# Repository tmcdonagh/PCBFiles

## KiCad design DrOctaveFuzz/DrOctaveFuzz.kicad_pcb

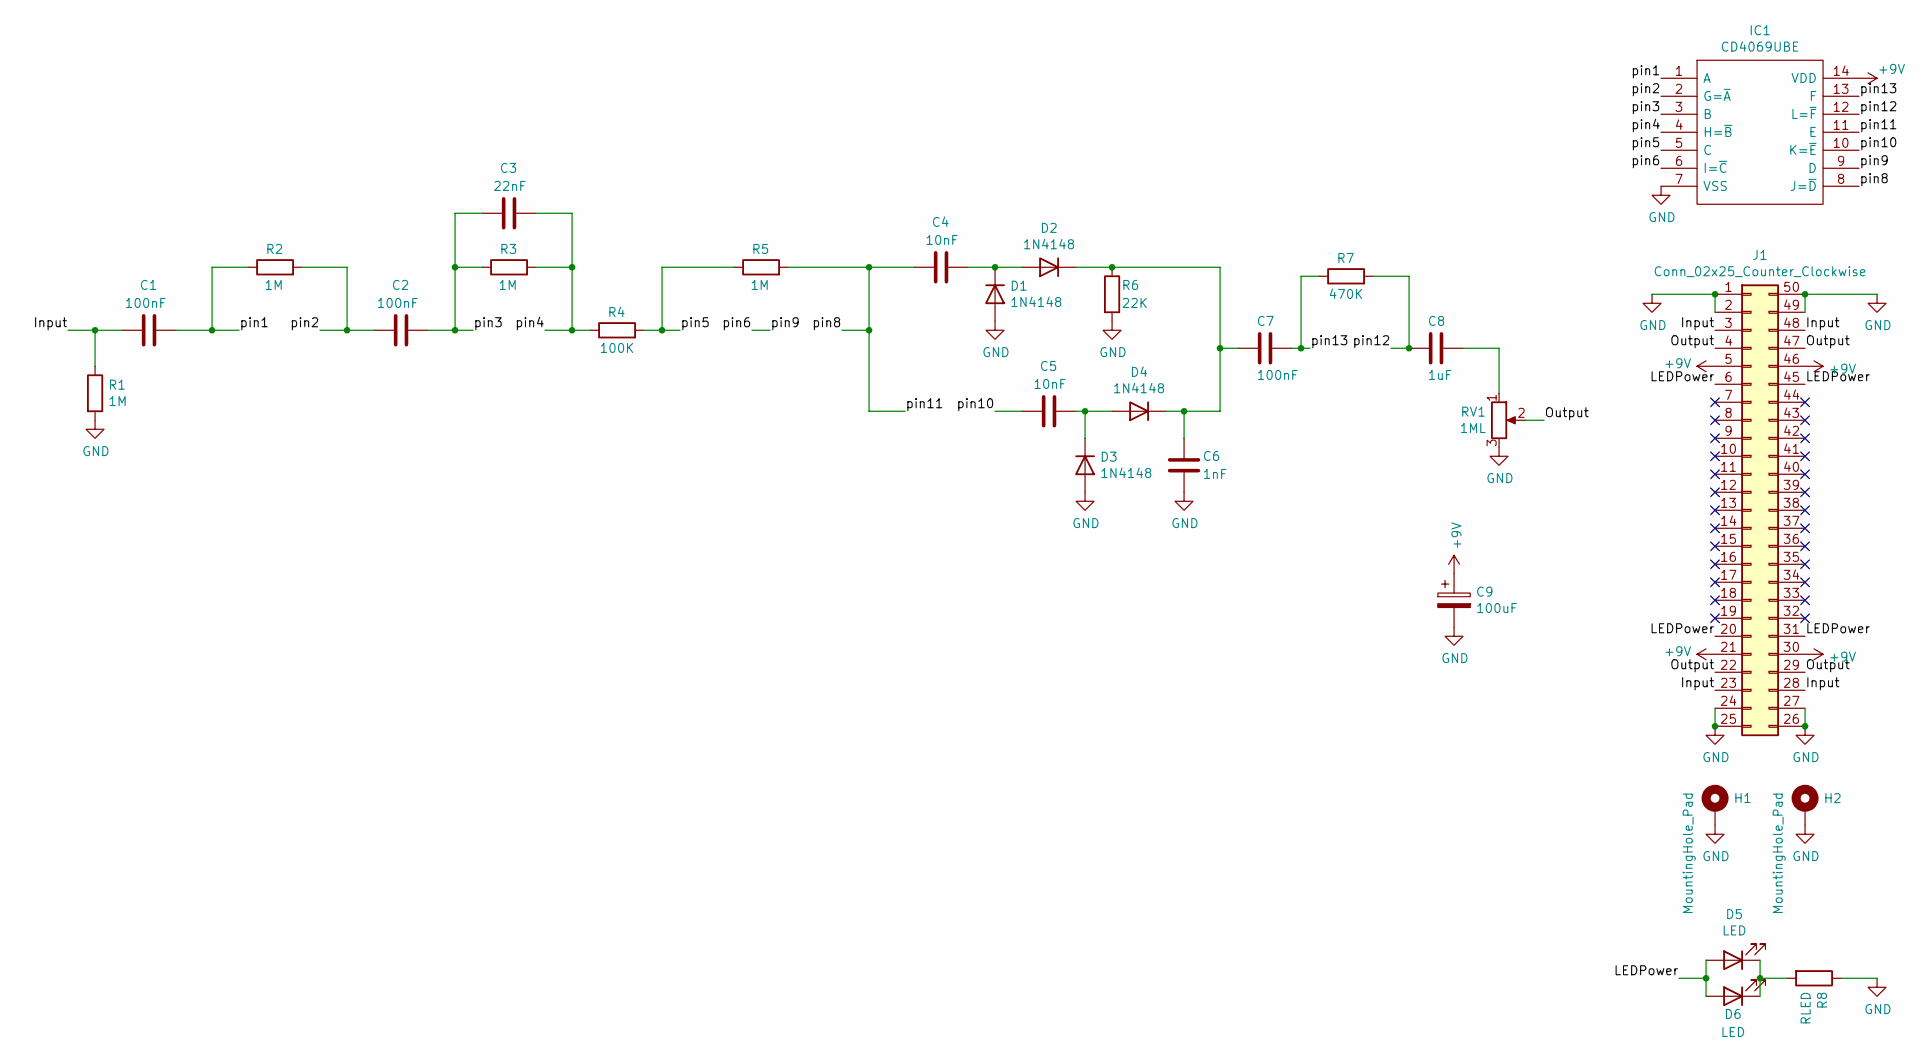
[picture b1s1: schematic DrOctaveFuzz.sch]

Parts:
C1, C2, C7: 100nF; C_Flat_L7.2_H6.5
C3: 22nF; C_Flat_L7.2_H6.5
C4, C5: 10nF; C_Flat_L7.2_H6.5
C6: 1nF; C_Flat_L7.2_H6.5
C8: 1uF; C_Flat_L7.2_H10
C9: 100uF; CP_Radial_D6.3mm_P2.00mm_L11.0mm
D1, D2, D3, D4: 1N4148; D_DO-35_SOD27_P7.62mm_Horizontal
D5, D6: LED; LED_D5.0mm
H1, H2: MountingHole_Pad; MountingHole_2.5mm_Pad
IC1: CD4069UBE; DIP-14_W7.62mm; Mouser Part Number 595-CD4069UBE
J1: Conn_02x25_Counter_Clockwise; N64-Connector-Wide
R1, R2, R3, R5: 1M; R_Axial_DIN0207_L6.3mm_D2.5mm_P10.16mm_Horizontal
R4: 100K; R_Axial_DIN0207_L6.3mm_D2.5mm_P10.16mm_Horizontal
R6: 22K; R_Axial_DIN0207_L6.3mm_D2.5mm_P10.16mm_Horizontal
R7: 470K; R_Axial_DIN0207_L6.3mm_D2.5mm_P10.16mm_Horizontal
R8: RLED; R_Axial_DIN0207_L6.3mm_D2.5mm_P10.16mm_Horizontal
RV1: 1ML; Potentiometer_Bourns_PTV09A-1_Single_Vertical

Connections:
+9V: C9.1, IC1.14 (VDD), J1.5, J1.21, J1.30, J1.46
/Input: C1.1, J1.3, J1.23, J1.28, J1.48, R1.1
/LEDPower: D5.2 (A), D6.2 (A), J1.6, J1.20, J1.31, J1.45
/Output: J1.4, J1.22, J1.29, J1.47, RV1.2
/pin1: C1.2, IC1.1 (A), R2.1
/pin2: C2.1, IC1.2 (G=~A), R2.2
/pin3: C2.2, C3.1, IC1.3 (B), R3.1
/pin4: C3.2, IC1.4 (H=~B), R3.2, R4.1
/pin5: IC1.5 (C), R4.2, R5.1
/pin6: IC1.6 (I=~C), IC1.9 (D)
/pin10: C5.1, IC1.10 (K=~E)
/pin11: C4.1, IC1.8 (J=~D), IC1.11 (E), R5.2
/pin12: C8.2, IC1.12 (L=~F), R7.2
/pin13: C7.1, IC1.13 (F), R7.1
GND: C6.2, C9.2, D1.2 (A), D3.2 (A), H1.1, H2.1, IC1.7 (VSS), J1.1, J1.2, J1.24, J1.25, J1.26, J1.27, J1.49, J1.50, R1.2, R6.2, R8.1, RV1.3
unnamed: C4.2, D1.1 (K), D2.2 (A)
unnamed: C5.2, D3.1 (K), D4.2 (A)
unnamed: C6.1, C7.2, D2.1 (K), D4.1 (K), R6.1
unnamed: C8.1, RV1.1
unnamed: D5.1 (K), D6.1 (K), R8.2

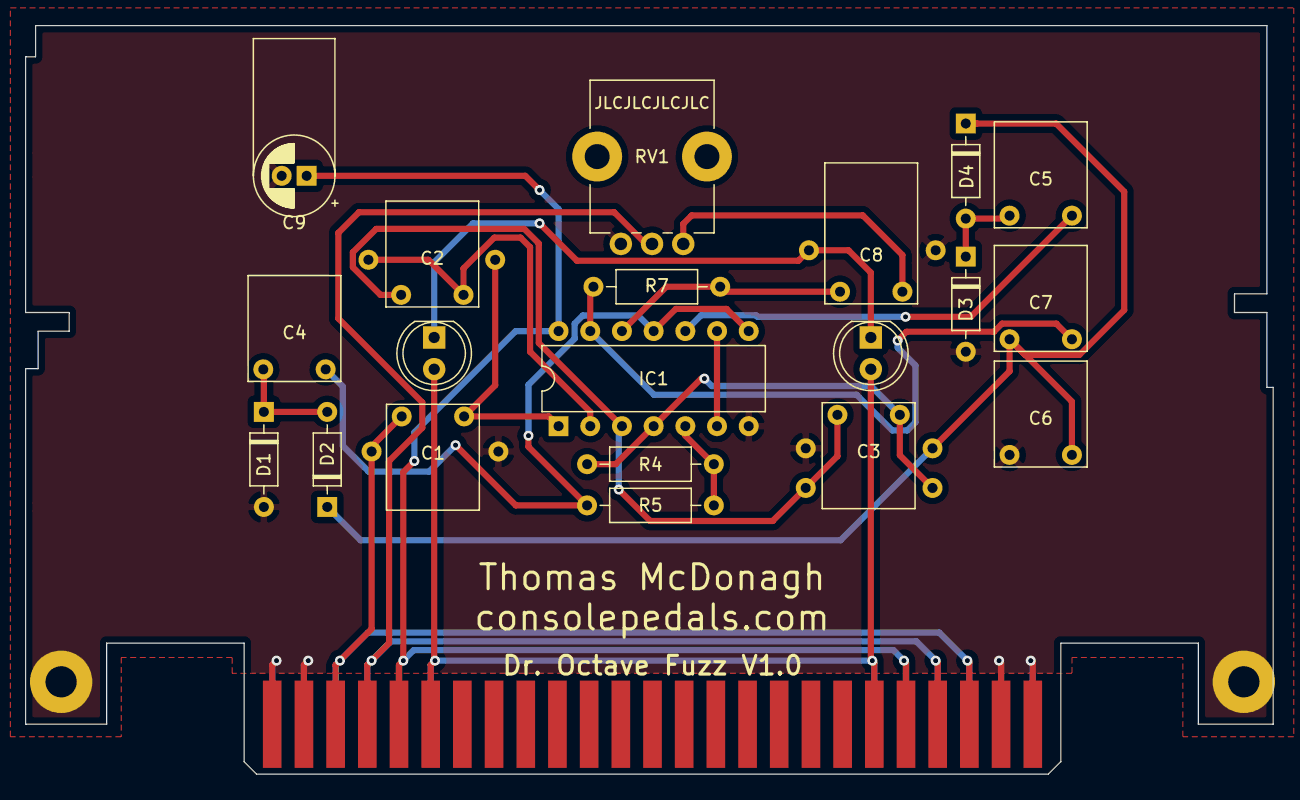
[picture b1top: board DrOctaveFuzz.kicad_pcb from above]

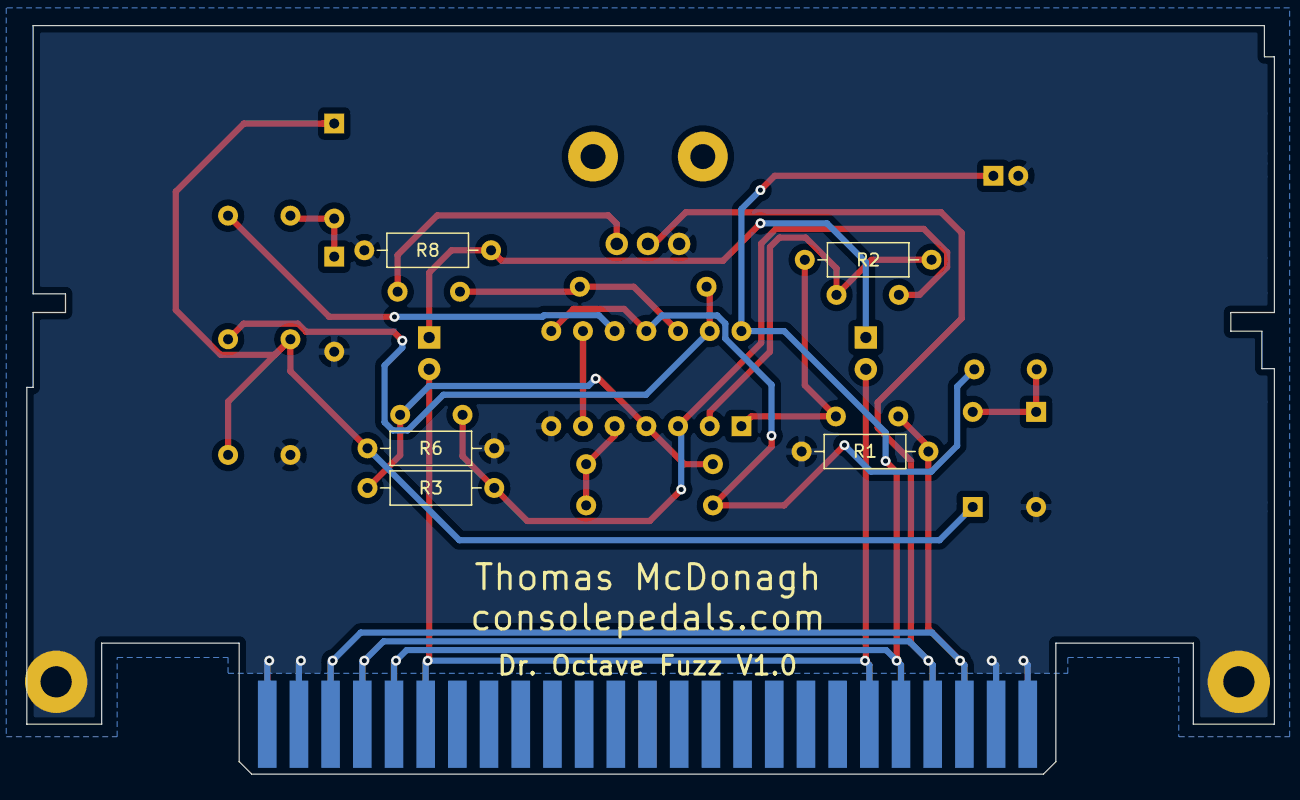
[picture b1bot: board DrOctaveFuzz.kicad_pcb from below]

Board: 2 copper layers, 100.0 x 60.0 mm, 28 parts (5 on the bottom side), 20 nets.

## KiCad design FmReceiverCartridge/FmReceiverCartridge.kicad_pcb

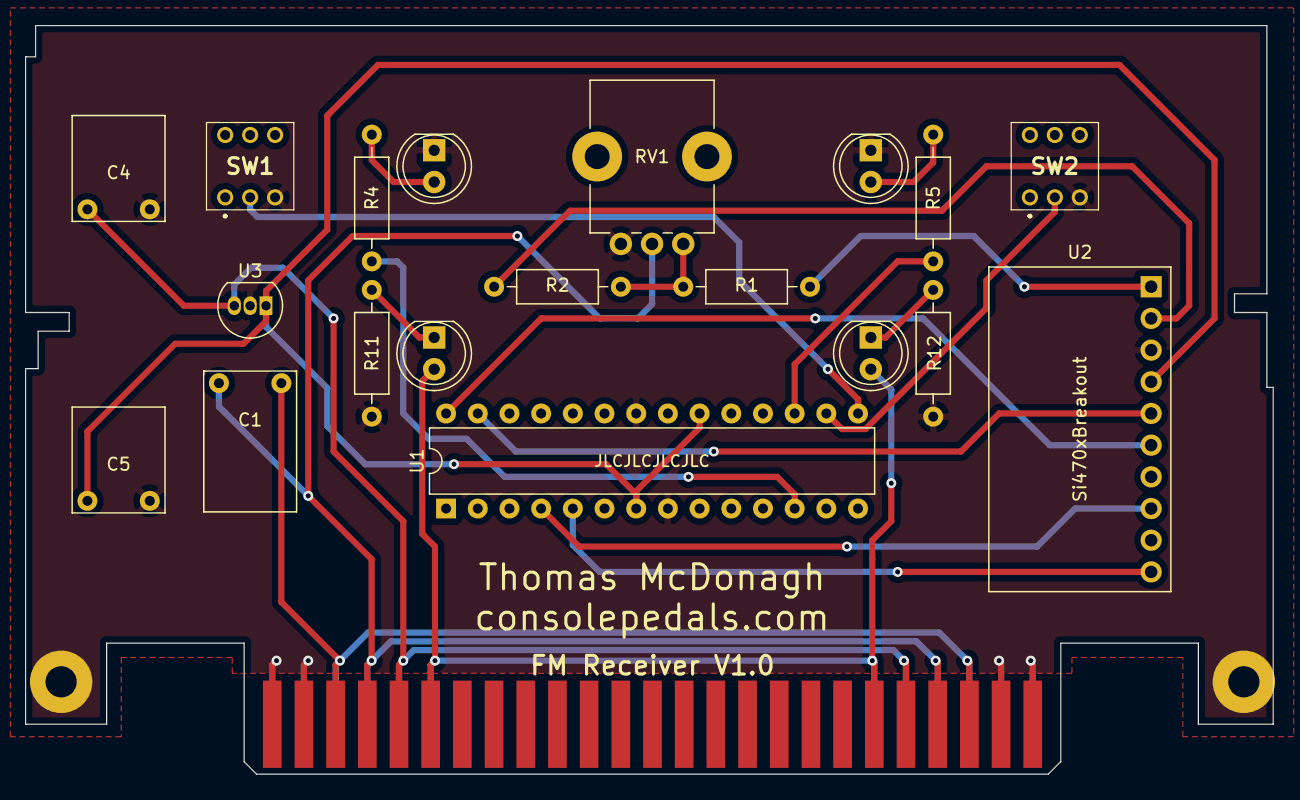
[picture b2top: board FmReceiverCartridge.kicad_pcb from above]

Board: 2 copper layers, 100.0 x 60.0 mm, 22 parts (0 on the bottom side), 21 nets.

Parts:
C1: 1uF; C_Flat_L7.2_H10
C4: 0.33uF; C_Flat_L7.2_H6.5
C5: 0.1uF; C_Flat_L7.2_H6.5
D1, D2, D4, D5: LED; LED_D5.0mm
H1, H2: MountingHole_Pad; MountingHole_2.5mm_Pad
J2: Conn_02x25_Counter_Clockwise; N64-Connector-Wide
R1, R2: 100R; R_Axial_DIN0207_L6.3mm_D2.5mm_P10.16mm_Horizontal
R4, R5, R11, R12: RLED; R_Axial_DIN0207_L6.3mm_D2.5mm_P10.16mm_Horizontal
RV1: 500K; Potentiometer_Bourns_PTV09A-1_Single_Vertical
SW1: SW_A; TL2230OAF140
SW2: SW_B; TL2230OAF140
U1: ATmega328P-PU; DIP-28_W7.62mm
U2: Si470xBreakout
U3: L78L33_TO92; TO-92_Inline

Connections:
+3V3: C5.2, U1.7, U1.20, U2.4, U3.1
+9V: C4.2, J2.5, J2.21, J2.30, J2.46, U3.3
/D2: U1.4, U2.8
/D3: U1.5, U2.10
/Input: C1.2, J2.3, J2.23, J2.28, J2.48
/LEDPower: D4.2, D5.2, J2.6, J2.20, J2.31, J2.45
/LED_A: R4.1, U1.12
/LED_B: R5.1, U1.17
/Output: C1.1, J2.4, J2.22, J2.29, J2.47, RV1.2
/SCL: U1.28, U2.6
/SDA: U1.27, U2.5
/SW_A: SW1.2, U1.15
/SW_B: SW2.2, U1.16
GND: C4.1, C5.1, D1.1, D2.1, H1.1, H2.1, J2.1, J2.2, J2.24, J2.25, J2.26, J2.27, J2.49, J2.50, R11.1, R12.2, RV1.3, SW1.3, SW2.3, U1.8, U1.22, U2.3, U3.2
unnamed: D1.2, R4.2
unnamed: D2.2, R5.2
unnamed: D4.1, R11.2
unnamed: D5.1, R12.1
unnamed: R1.1, R2.2, RV1.1
unnamed: R1.2, U2.1
unnamed: R2.1, U2.2

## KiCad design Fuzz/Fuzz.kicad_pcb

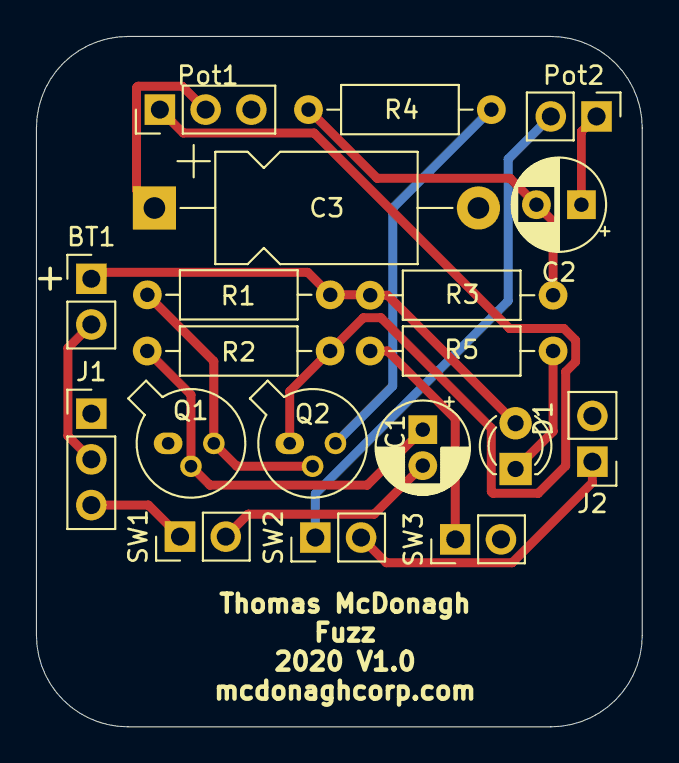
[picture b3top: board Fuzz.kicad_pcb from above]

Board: 2 copper layers, 33.7 x 38.4 mm, 19 parts (0 on the bottom side), 16 nets.

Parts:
BT1: Battery; PinHeader_1x02_P2.54mm_Vertical
C1: 2.2uf; CP_Radial_D5.0mm_P2.00mm
C2: 0.01uf; CP_Radial_D5.0mm_P2.50mm
C3: 22uf; CP_Axial_L11.0mm_D6.0mm_P18.00mm_Horizontal
D1: LED; LED_D3.0mm
J1: AudioJack3; PinHeader_1x03_P2.54mm_Vertical
J2: AudioJack2; PinHeader_1x02_P2.54mm_Vertical
Pot1: 1K; PinHeader_1x03_P2.54mm_Vertical
Pot2: 500K; PinHeader_1x02_P2.54mm_Vertical
Q1, Q2: BC109; TO-18-3
R1: 33K; R_Axial_DIN0207_L6.3mm_D2.5mm_P10.16mm_Horizontal
R2, R5: 100K; R_Axial_DIN0207_L6.3mm_D2.5mm_P10.16mm_Horizontal
R3: 330; R_Axial_DIN0207_L6.3mm_D2.5mm_P10.16mm_Horizontal
R4: 8.2K; R_Axial_DIN0207_L6.3mm_D2.5mm_P10.16mm_Horizontal
SW1, SW2, SW3: SW_SPST; PinHeader_1x02_P2.54mm_Vertical

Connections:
GND: C3.2, J1.1, J2.2, Pot1.3, Q1.1, SW3.2
unnamed: BT1.1, D1.2, R1.2, R3.2
unnamed: BT1.2, J1.2
unnamed: C1.1, Q1.2, R2.1
unnamed: C1.2, SW1.2
unnamed: C2.1, Pot2.1
unnamed: C2.2, R3.1, R4.1
unnamed: C3.1, Pot1.2
unnamed: D1.1, R5.2
unnamed: J1.3, SW1.1
unnamed: J2.1, SW2.2
unnamed: Pot1.1, Q2.1, R2.2
unnamed: Pot2.2, SW2.1
unnamed: Q1.3, Q2.2, R1.1
unnamed: Q2.3, R4.2
unnamed: R5.1, SW3.1

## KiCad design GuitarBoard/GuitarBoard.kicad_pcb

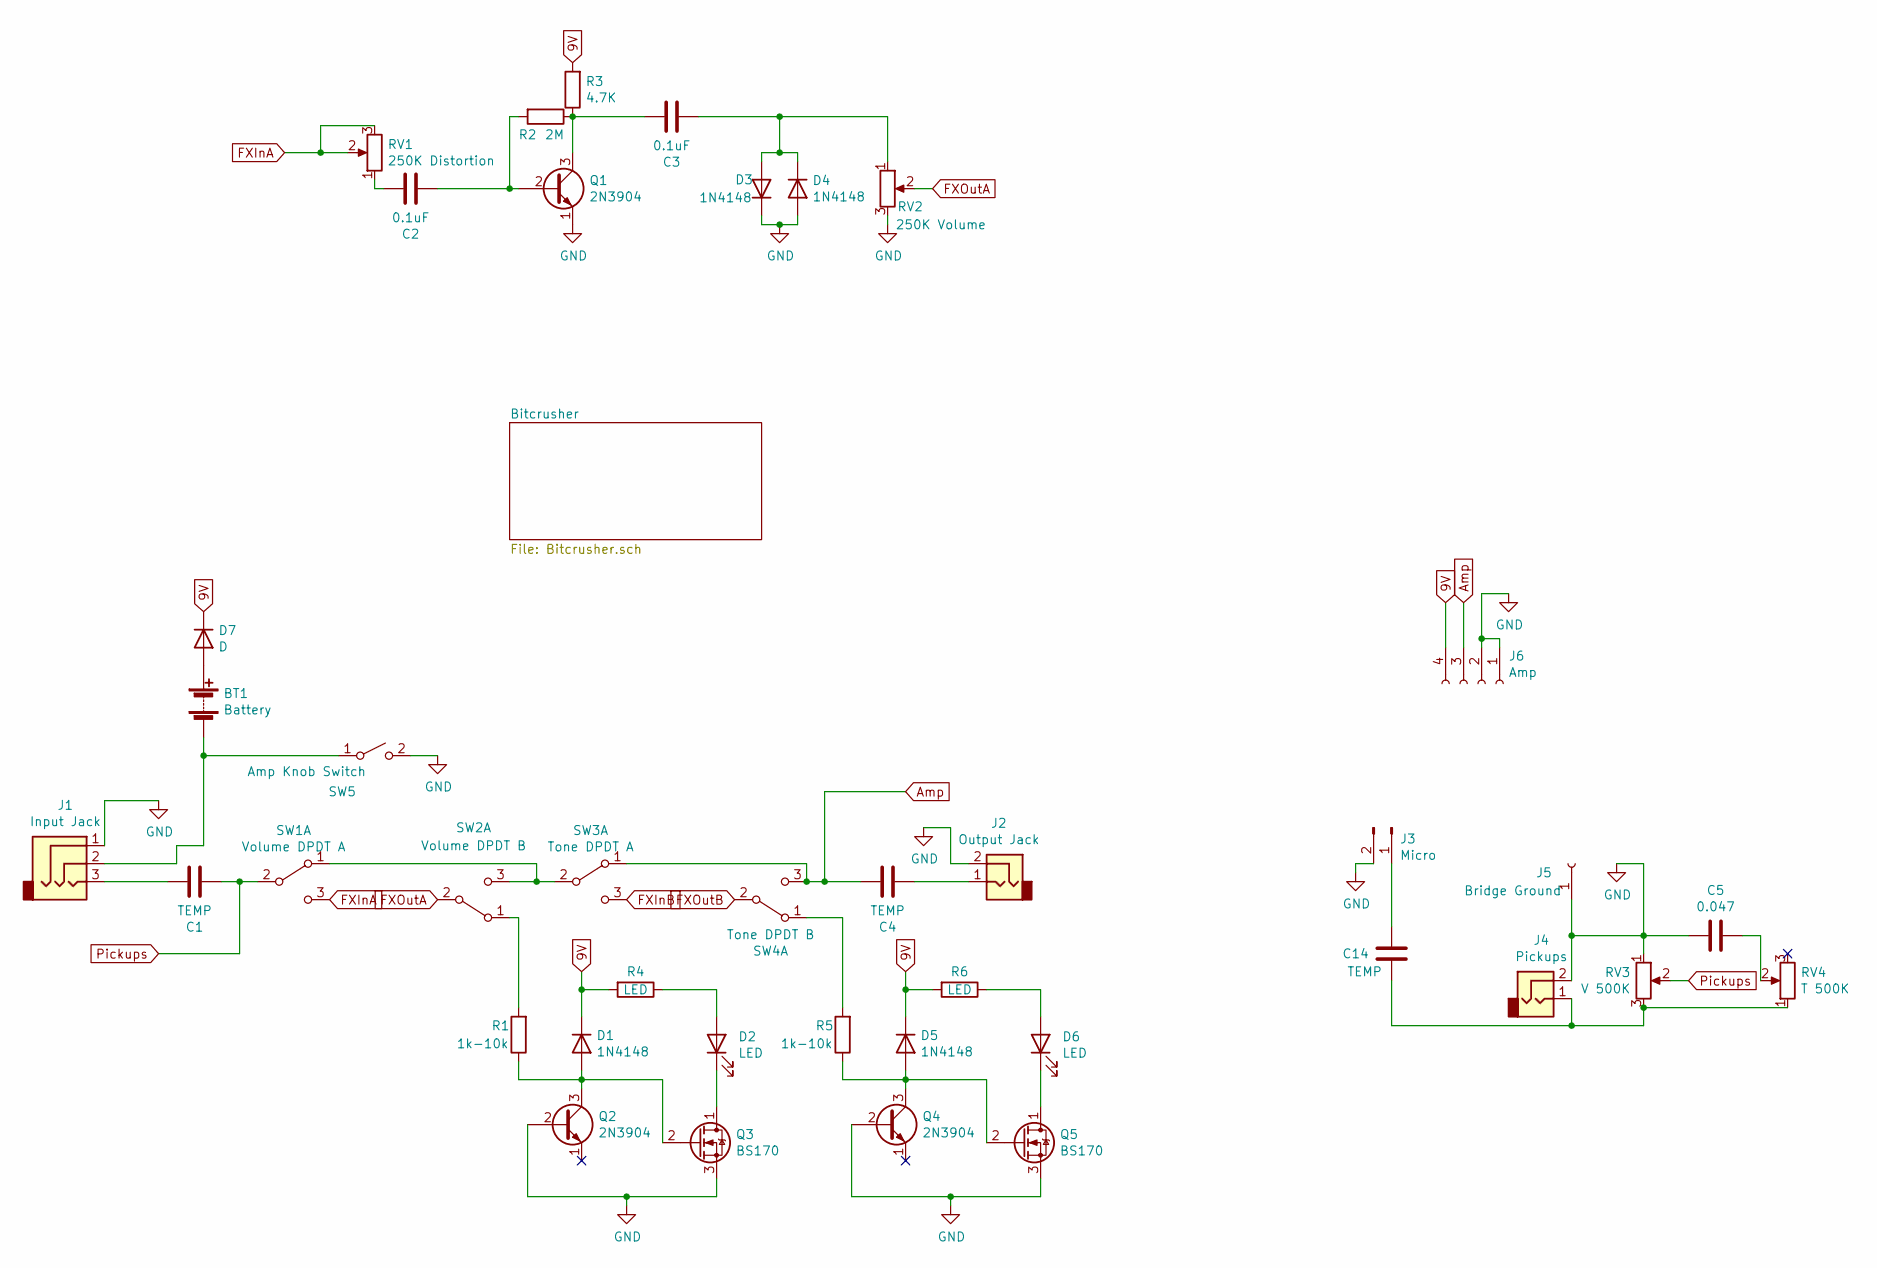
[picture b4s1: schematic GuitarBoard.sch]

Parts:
BT1: Battery; TerminalBlock_bornier-2_P5.08mm
C1, C4: TEMP; C_Flat_L7.2_H10
C2, C3: 0.1uF; C_Rect_L7.2mm_W2.5mm_P5.00mm_FKS2_FKP2_MKS2_MKP2
C5: 0.047; C_Rect_L7.2mm_W2.5mm_P5.00mm_FKS2_FKP2_MKS2_MKP2
C14: TEMP; C_Rect_L7.2mm_W2.5mm_P5.00mm_FKS2_FKP2_MKS2_MKP2
D1, D3, D4, D5: 1N4148; D_DO-35_SOD27_P7.62mm_Horizontal
D2, D6: LED; PinSocket_1x02_P2.54mm_Vertical
D7: D; D_DO-41_SOD81_P10.16mm_Horizontal
J1: Input Jack; PinSocket_1x03_P2.54mm_Vertical
J2: Output Jack; PinSocket_1x02_P2.54mm_Vertical
J3: Micro; TerminalBlock_bornier-2_P5.08mm
J4: Pickups; TerminalBlock_bornier-2_P5.08mm
J5: Bridge Ground; TerminalBlock_bornier-2_P5.08mm
J6: Amp; TerminalBlock_bornier-4_P5.08mm
Q1, Q2, Q4: 2N3904; TO-92_Inline
Q3, Q5: BS170; TO-92_Inline
R1, R5: 1k-10k; R_Axial_DIN0207_L6.3mm_D2.5mm_P10.16mm_Horizontal
R2: 2M; R_Axial_DIN0207_L6.3mm_D2.5mm_P10.16mm_Horizontal
R3: 4.7K; R_Axial_DIN0207_L6.3mm_D2.5mm_P10.16mm_Horizontal
R4, R6: LED; R_Axial_DIN0207_L6.3mm_D2.5mm_P10.16mm_Horizontal
RV1: 250K Distortion; Potentiometer_Bourns_3386F_Vertical
RV2: 250K Volume; Potentiometer_Bourns_3386F_Vertical
RV3: V 500K; PinSocket_1x03_P2.54mm_Vertical
RV4: T 500K; PinSocket_1x03_P2.54mm_Vertical
SW1: Volume DPDT A; PinSocket_1x03_P2.54mm_Vertical
SW2: Volume DPDT B; PinSocket_1x03_P2.54mm_Vertical
SW3: Tone DPDT A; PinSocket_1x03_P2.54mm_Vertical
SW4: Tone DPDT B; PinSocket_1x03_P2.54mm_Vertical
SW5: Amp Knob Switch; PinSocket_1x02_P2.54mm_Vertical

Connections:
9V: D1.1 (K), D5.1 (K), D7.1 (K), J6.4, R3.2, R4.2, R6.2; also elsewhere on the board
Amp: C4.1, J6.3, SW3.1 (A), SW4.3 (C)
FXInA: RV1.2, RV1.3, SW1.3 (C)
FXInB: SW3.3 (C); also elsewhere on the board
FXOutA: RV2.2, SW2.2 (B)
FXOutB: SW4.2 (B); also elsewhere on the board
GND: C5.2, D3.1 (K), D4.2 (A), J1.1, J2.2, J3.2, J4.2, J5.1, J6.1, J6.2, Q1.1 (E), Q2.2 (B), Q3.3 (S), Q4.2 (B), Q5.3 (S), RV2.3, RV3.1, SW5.2 (B); also elsewhere on the board
unnamed: BT1.1 (+), D7.2 (A)
unnamed: BT1.2 (-), J1.2, SW5.1 (A)
unnamed: C1.1, J1.3
unnamed: C2.1, RV1.1
unnamed: C2.2, Q1.2 (B), R2.2
unnamed: C3.1, Q1.3 (C), R2.1, R3.1
unnamed: C3.2, D3.2 (A), D4.1 (K), RV2.1
unnamed: C4.2, J2.1
unnamed: C5.1, RV4.2
unnamed: C14.1, J3.1
unnamed: C14.2, J4.1, RV3.3, RV4.1
unnamed: D1.2 (A), Q2.3 (C), Q3.2 (G), R1.1
unnamed: D2.1 (K), Q3.1 (D)
unnamed: D2.2 (A), R4.1
unnamed: D5.2 (A), Q4.3 (C), Q5.2 (G), R5.1
unnamed: D6.1 (K), Q5.1 (D)
unnamed: D6.2 (A), R6.1
unnamed: R1.2, SW2.1 (A)
unnamed: R5.2, SW4.1 (A)
unnamed: SW1.1 (A), SW2.3 (C), SW3.2 (B)
Pickups: C1.2, RV3.2, SW1.2 (B)

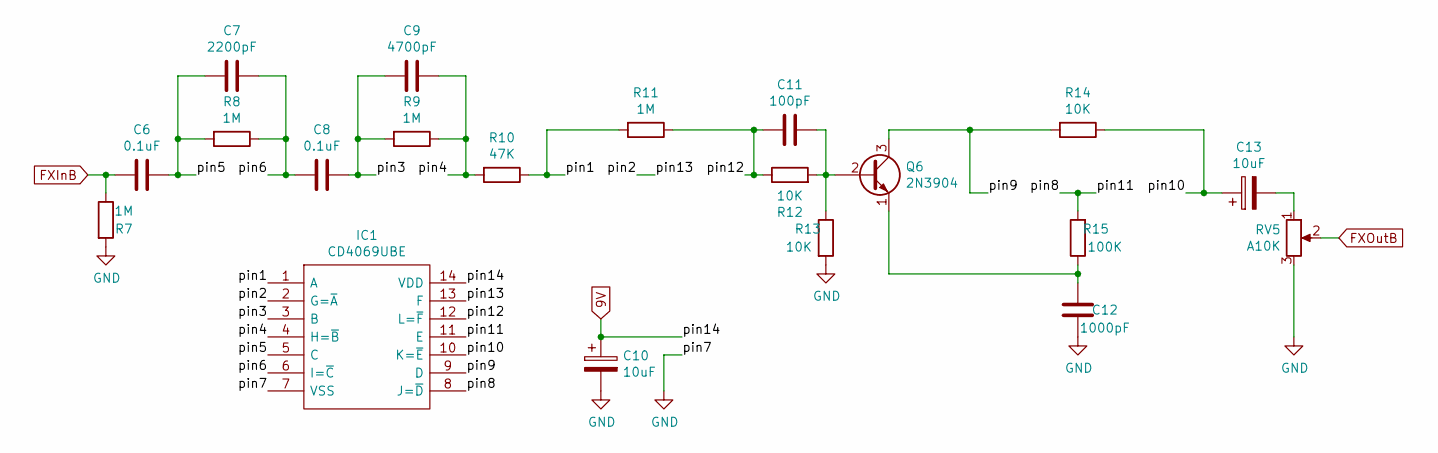
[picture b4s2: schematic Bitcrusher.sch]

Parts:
C6, C8: 0.1uF; C_Rect_L7.2mm_W2.5mm_P5.00mm_FKS2_FKP2_MKS2_MKP2
C7: 2200pF; C_Rect_L7.2mm_W2.5mm_P5.00mm_FKS2_FKP2_MKS2_MKP2
C9: 4700pF; C_Rect_L7.2mm_W2.5mm_P5.00mm_FKS2_FKP2_MKS2_MKP2
C10, C13: 10uF; CP_Radial_D6.3mm_P2.50mm
C11: 100pF; C_Rect_L7.2mm_W2.5mm_P5.00mm_FKS2_FKP2_MKS2_MKP2
C12: 1000pF; C_Rect_L7.2mm_W2.5mm_P5.00mm_FKS2_FKP2_MKS2_MKP2
IC1: CD4069UBE; DIP794W53P254L1930H508Q14N; Mouser Part Number 595-CD4069UBE
Q6: 2N3904; TO-92_Inline
R7, R8, R9, R11: 1M; R_Axial_DIN0207_L6.3mm_D2.5mm_P10.16mm_Horizontal
R10: 47K; R_Axial_DIN0207_L6.3mm_D2.5mm_P10.16mm_Horizontal
R12, R13, R14: 10K; R_Axial_DIN0207_L6.3mm_D2.5mm_P10.16mm_Horizontal
R15: 100K; R_Axial_DIN0207_L6.3mm_D2.5mm_P10.16mm_Horizontal
RV5: A10K; Potentiometer_Bourns_3386F_Vertical

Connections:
9V: C10.1, IC1.14 (VDD); also elsewhere on the board
/Bitcrusher/pin1: IC1.1 (A), R10.1, R11.2
/Bitcrusher/pin3: C8.1, C9.2, IC1.3 (B), R9.2
/Bitcrusher/pin4: C9.1, IC1.4 (H=~B), R9.1, R10.2
/Bitcrusher/pin5: C6.1, C7.2, IC1.5 (C), R8.2
/Bitcrusher/pin6: C7.1, C8.2, IC1.6 (I=~C), R8.1
/Bitcrusher/pin9: IC1.9 (D), Q6.3 (C), R14.2
/Bitcrusher/pin10: C13.1, IC1.10 (K=~E), R14.1
/Bitcrusher/pin11: IC1.8 (J=~D), IC1.11 (E), R15.2
/Bitcrusher/pin12: C11.2, IC1.12 (L=~F), R11.1, R12.1
/Bitcrusher/pin13: IC1.2 (G=~A), IC1.13 (F)
FXInB: C6.2, R7.1; also elsewhere on the board
FXOutB: RV5.2; also elsewhere on the board
GND: C10.2, C12.1, IC1.7 (VSS), R7.2, R13.2, RV5.3; also elsewhere on the board
unnamed: C11.1, Q6.2 (B), R12.2, R13.1
unnamed: C12.2, Q6.1 (E), R15.1
unnamed: C13.2, RV5.1

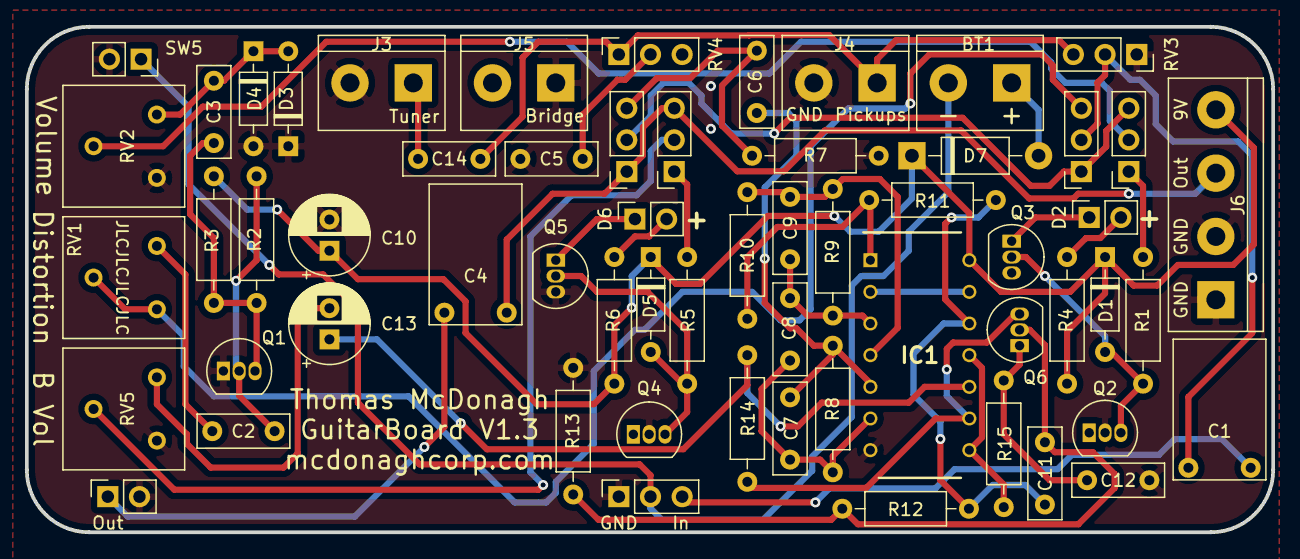
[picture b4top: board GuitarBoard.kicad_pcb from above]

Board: 2 copper layers, 100.0 x 40.6 mm, 60 parts (0 on the bottom side), 41 nets.

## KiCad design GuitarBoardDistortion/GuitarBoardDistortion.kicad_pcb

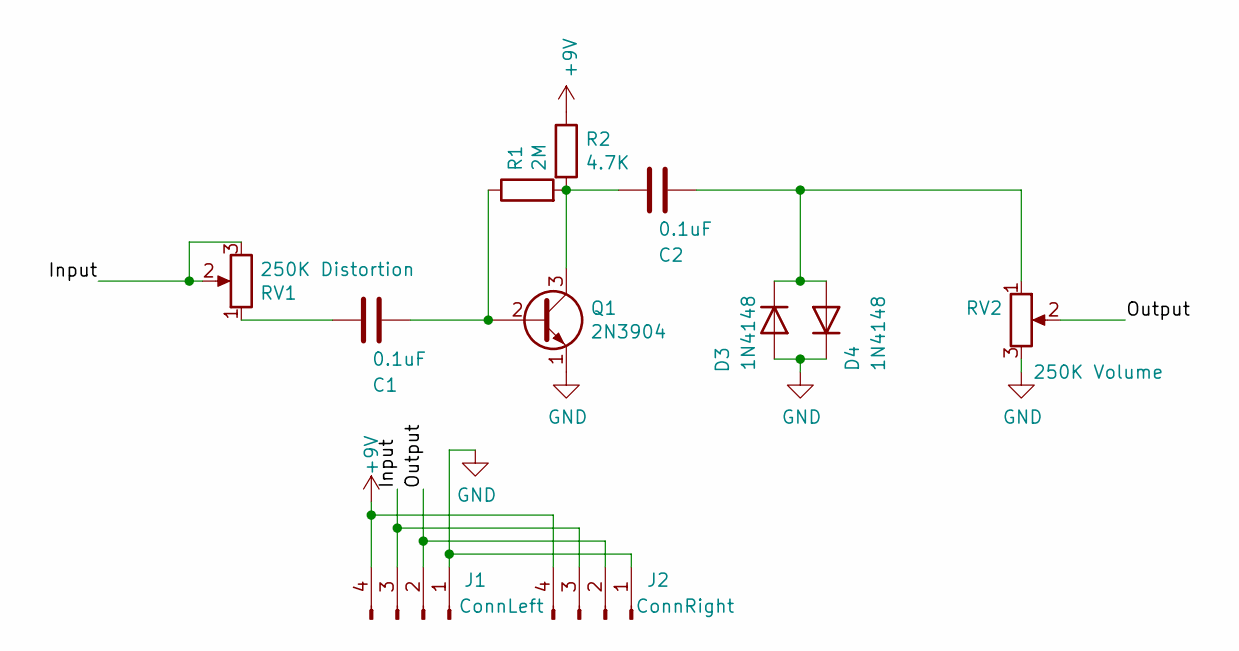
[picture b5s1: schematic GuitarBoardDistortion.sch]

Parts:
C1, C2: 0.1uF; C_Disc_D10.5mm_W5.0mm_P7.50mm
D3, D4: 1N4148; D_DO-35_SOD27_P7.62mm_Horizontal
J1: ConnLeft; PinSocket_1x04_P2.54mm_Vertical
J2: ConnRight; PinSocket_1x04_P2.54mm_Vertical
Q1: 2N3904; TO-92_Inline
R1: 2M; R_Axial_DIN0207_L6.3mm_D2.5mm_P10.16mm_Horizontal
R2: 4.7K; R_Axial_DIN0207_L6.3mm_D2.5mm_P10.16mm_Horizontal
RV1: 250K Distortion; Potentiometer_Bourns_3386F_Vertical
RV2: 250K Volume; Potentiometer_Bourns_3386F_Vertical

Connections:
+9V: J1.4, J2.4, R2.1
/Input: J1.3, J2.3, RV1.2, RV1.3
/Output: J1.2, J2.2, RV2.2
GND: D3.2 (A), D4.1 (K), J1.1, J2.1, Q1.1 (E), RV2.3
unnamed: C1.1, Q1.2 (B), R1.1
unnamed: C1.2, RV1.1
unnamed: C2.1, D3.1 (K), D4.2 (A), RV2.1
unnamed: C2.2, Q1.3 (C), R1.2, R2.2

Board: 2 copper layers, 11 parts (0 on the bottom side), 8 nets, no tracks yet.

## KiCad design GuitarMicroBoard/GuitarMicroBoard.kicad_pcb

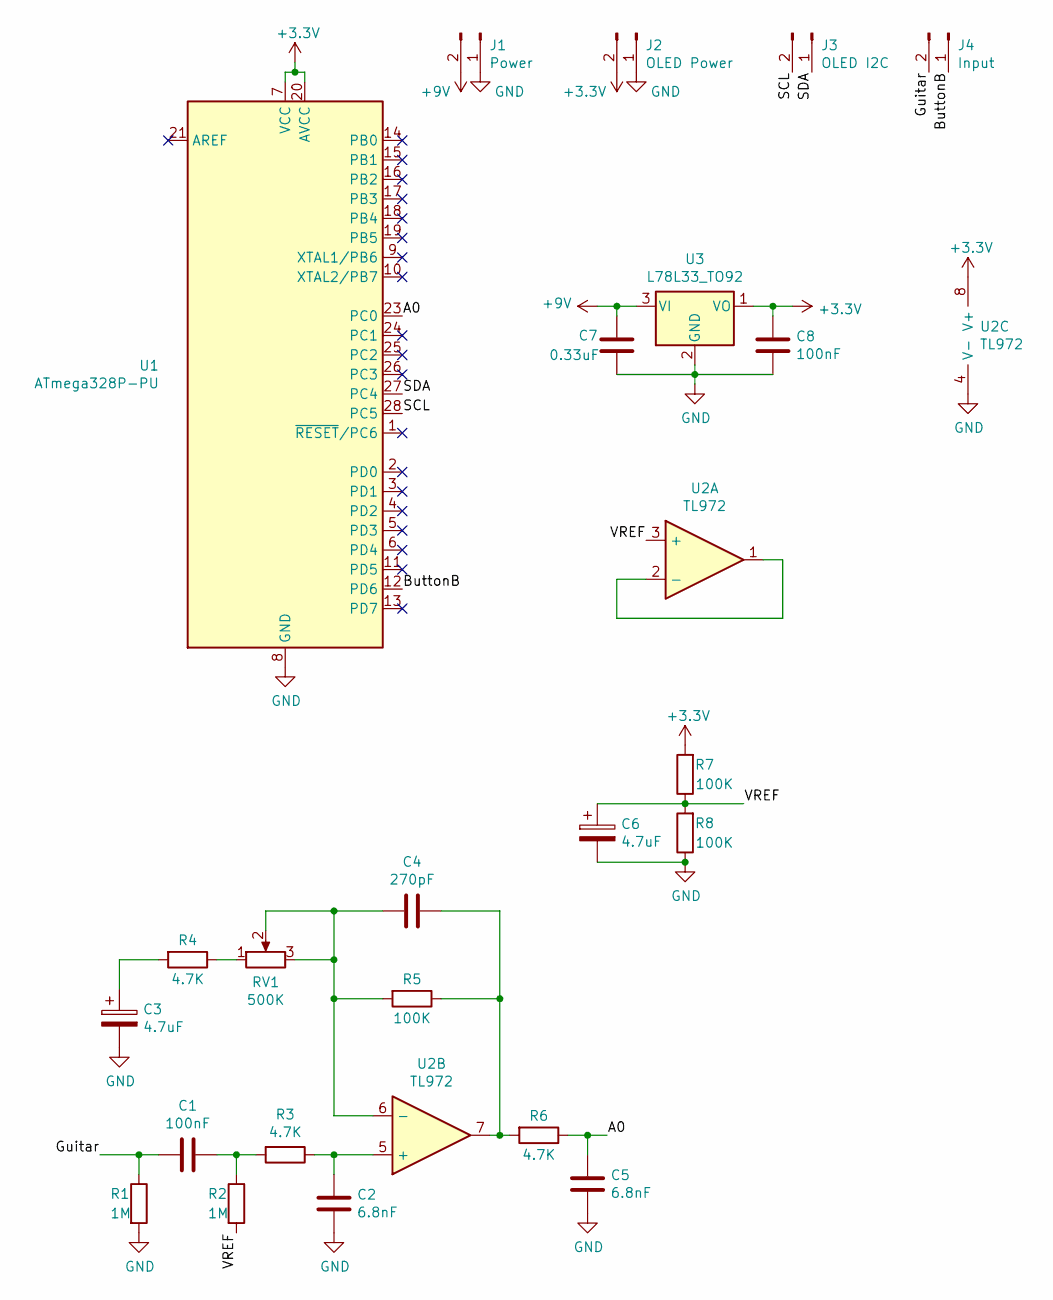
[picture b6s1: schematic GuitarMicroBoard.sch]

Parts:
C1, C8: 100nF; C_Rect_L7.2mm_W2.5mm_P5.00mm_FKS2_FKP2_MKS2_MKP2
C2, C5: 6.8nF; C_Rect_L7.2mm_W2.5mm_P5.00mm_FKS2_FKP2_MKS2_MKP2
C3, C6: 4.7uF; CP_Radial_D5.0mm_P2.00mm_L11.0mm
C4: 270pF; C_Rect_L7.2mm_W2.5mm_P5.00mm_FKS2_FKP2_MKS2_MKP2
C7: 0.33uF; C_Rect_L7.2mm_W2.5mm_P5.00mm_FKS2_FKP2_MKS2_MKP2
J1: Power; PinSocket_1x02_P2.54mm_Vertical
J2: OLED Power; TerminalBlock_bornier-2_P5.08mm
J3: OLED I2C; TerminalBlock_bornier-2_P5.08mm
J4: Input; TerminalBlock_bornier-2_P5.08mm
R1, R2: 1M; R_Axial_DIN0207_L6.3mm_D2.5mm_P10.16mm_Horizontal
R3, R4, R6: 4.7K; R_Axial_DIN0207_L6.3mm_D2.5mm_P10.16mm_Horizontal
R5, R7, R8: 100K; R_Axial_DIN0207_L6.3mm_D2.5mm_P10.16mm_Horizontal
RV1: 500K; Potentiometer_Bourns_3386F_Vertical
U1: ATmega328P-PU; DIP-28_W7.62mm
U2: TL972; DIP-8_W7.62mm
U3: L78L33_TO92; TO-92_Inline

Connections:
+3V3: C8.1, J2.2, R7.2, U1.7 (VCC), U1.20 (AVCC), U2.8 (V+), U3.1 (VO)
+9V: C7.1, J1.2, U3.3 (VI)
/A0: C5.1, R6.1, U1.23 (PC0)
/ButtonB: J4.1, U1.12 (PD6)
/Guitar: C1.2, J4.2, R1.1
/SCL: J3.2, U1.28 (PC5)
/SDA: J3.1, U1.27 (PC4)
/VREF: C6.1, R2.2, R7.1, R8.2, U2.3 (+)
GND: C2.1, C3.2, C5.2, C6.2, C7.2, C8.2, J1.1, J2.1, R1.2, R8.1, U1.8 (GND), U1.22 (GND), U2.4 (V-), U3.2 (GND)
unnamed: C1.1, R2.1, R3.2
unnamed: C2.2, R3.1, U2.5 (+)
unnamed: C3.1, R4.2
unnamed: C4.1, R5.2, RV1.2, RV1.3, U2.6 (-)
unnamed: C4.2, R5.1, R6.2, U2.7
unnamed: R4.1, RV1.1
unnamed: U2.1, U2.2 (-)

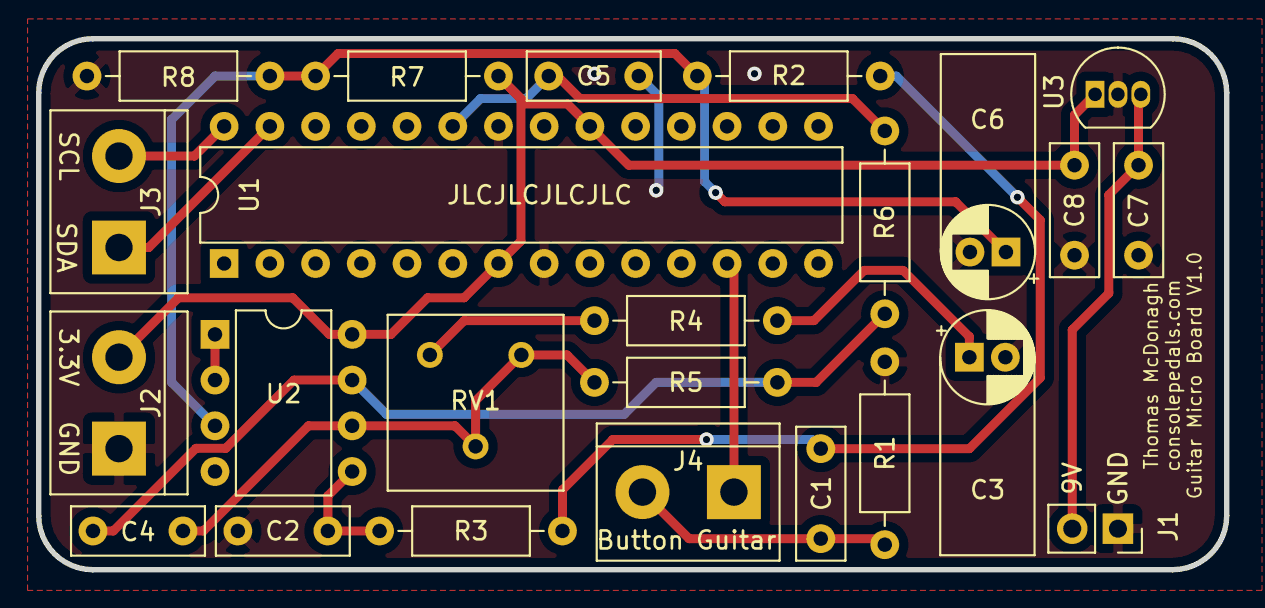
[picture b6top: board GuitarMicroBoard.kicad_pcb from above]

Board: 2 copper layers, 66.0 x 29.5 mm, 24 parts (0 on the bottom side), 16 nets.

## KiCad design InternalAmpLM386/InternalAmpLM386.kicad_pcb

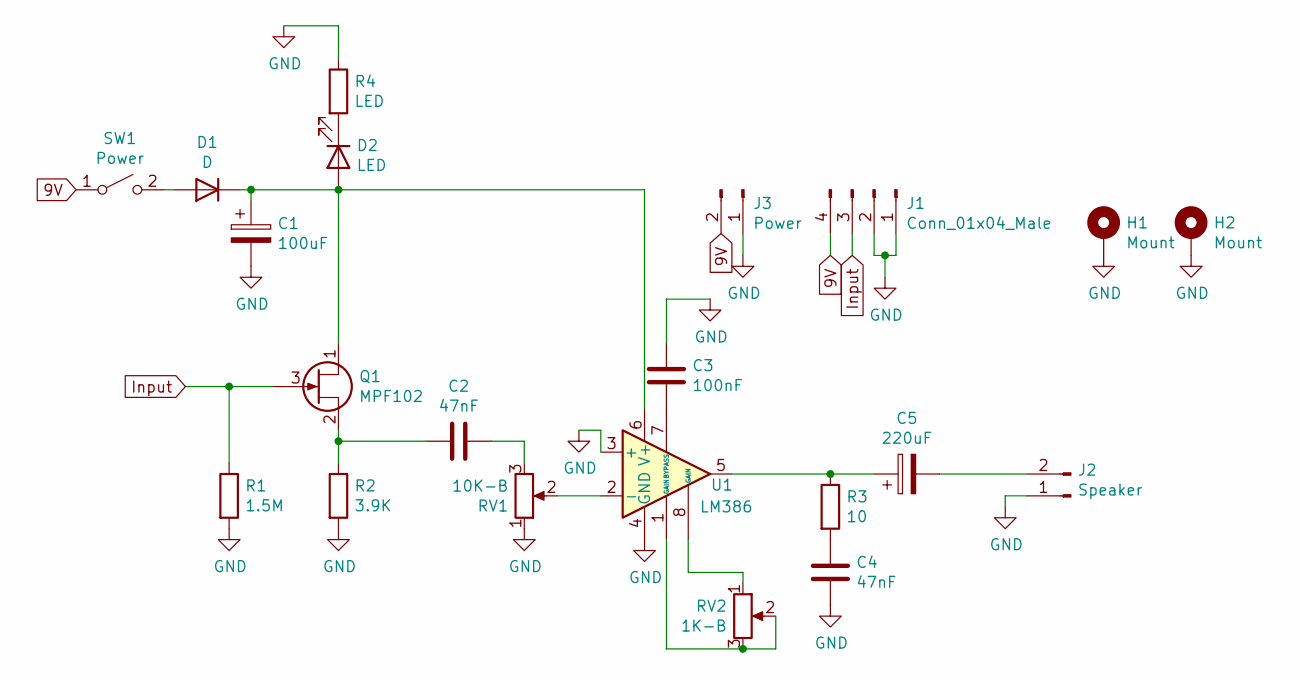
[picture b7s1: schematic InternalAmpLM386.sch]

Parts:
C1: 100uF; CP_Radial_D8.0mm_P3.50mm
C2, C4: 47nF; C_Flat_L7.2_H6.5
C3: 100nF; C_Flat_L7.2_H6.5
C5: 220uF; CP_Radial_D10.0mm_P5.00mm
D1: D; D_DO-41_SOD81_P10.16mm_Horizontal
D2: LED; LED_D5.0mm
H1, H2: Mount; MountingHole_2.7mm_Pad
J1: Conn_01x04_Male; PinSocket_1x04_P2.54mm_Vertical
J2: Speaker; PinSocket_1x02_P2.54mm_Vertical
J3: Power; PinSocket_1x02_P2.54mm_Vertical
Q1: MPF102; TO-92L_Inline
R1: 1.5M; R_Axial_DIN0207_L6.3mm_D2.5mm_P10.16mm_Horizontal
R2: 3.9K; R_Axial_DIN0207_L6.3mm_D2.5mm_P10.16mm_Horizontal
R3: 10; R_Axial_DIN0207_L6.3mm_D2.5mm_P10.16mm_Horizontal
R4: LED; R_Axial_DIN0207_L6.3mm_D2.5mm_P10.16mm_Horizontal
RV1: 10K-B; PinHeader_1x03_P2.54mm_Vertical
RV2: 1K-B; Potentiometer_Bourns_3386F_Vertical
SW1: Power; PinHeader_1x02_P2.54mm_Vertical
U1: LM386; DIP-8_W7.62mm

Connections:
9V: J1.4, J3.2, SW1.1 (A)
GND: C1.2, C3.1, C4.2, H1.1, H2.1, J1.1, J1.2, J2.1, J3.1, R1.2, R2.2, R4.1, RV1.1, U1.3 (+), U1.4 (GND)
Input: J1.3, Q1.3 (G), R1.1
unnamed: C1.1, D1.1 (K), D2.2 (A), Q1.1 (D), U1.6 (V+)
unnamed: C2.1, Q1.2 (S), R2.1
unnamed: C2.2, RV1.3
unnamed: C3.2, U1.7 (BYPASS)
unnamed: C4.1, R3.2
unnamed: C5.1, R3.1, U1.5
unnamed: C5.2, J2.2
unnamed: D1.2 (A), SW1.2 (B)
unnamed: D2.1 (K), R4.2
unnamed: RV1.2, U1.2 (-)
unnamed: RV2.1, U1.8 (GAIN)
unnamed: RV2.2, RV2.3, U1.1 (GAIN)
